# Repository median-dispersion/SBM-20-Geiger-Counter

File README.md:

# SBM-20 Geiger Counter

### ⚠️  DISCLAIMER
This is a hobbyist project and should not be used to accurately determine radiation levels, especially not if those radiation levels are potentially dangerous and or lethal!

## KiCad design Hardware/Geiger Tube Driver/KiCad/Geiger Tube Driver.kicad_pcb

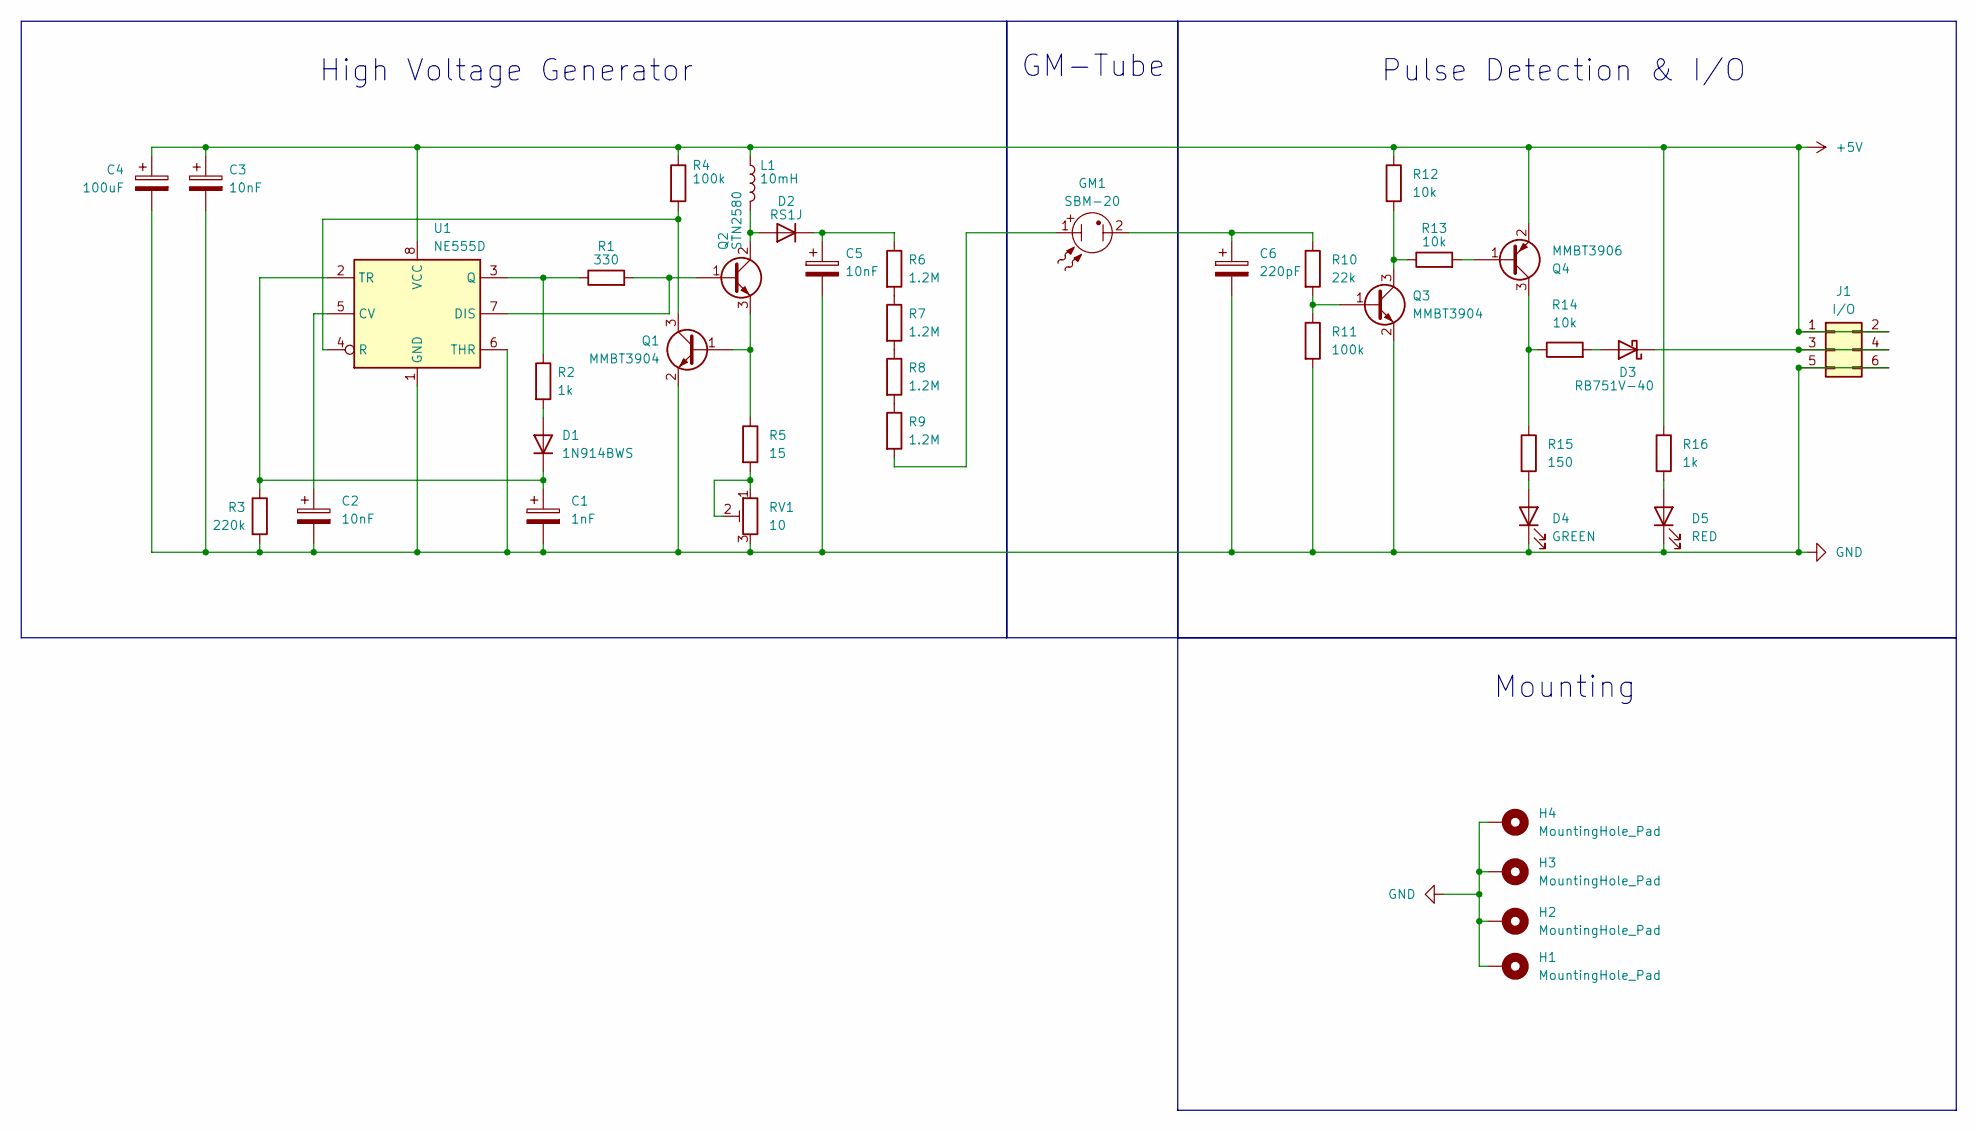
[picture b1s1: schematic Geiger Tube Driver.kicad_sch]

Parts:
C1: 1nF; C_1206_3216Metric_Pad1.33x1.80mm_HandSolder
C2, C3, C5: 10nF; C_1206_3216Metric_Pad1.33x1.80mm_HandSolder
C4: 100uF; CP_Elec_6.3x5.4
C6: 220pF; C_1206_3216Metric_Pad1.33x1.80mm_HandSolder
D1: 1N914BWS; D_SOD-323_HandSoldering
D2: RS1J; SMA_HV_Handsoldering
D3: RB751V-40; D_SOD-323_HandSoldering
D4: GREEN; LED_1206_3216Metric_Pad1.42x1.75mm_HandSolder
D5: RED; LED_1206_3216Metric_Pad1.42x1.75mm_HandSolder
GM1: SBM-20
H1, H2, H3, H4: MountingHole_Pad; MountingHole_3.2mm_M3_Pad_Via
J1: I/O; PinHeader_2x03_P2.54mm_Vertical
L1: 10mH; 8065_Handsoldering
Q1, Q3: MMBT3904; SOT-23_Handsoldering
Q2: STN2580; SOT-223-3_TabPin2
Q4: MMBT3906; SOT-23_Handsoldering
R1: 330; R_1206_3216Metric_Pad1.30x1.75mm_HandSolder
R2, R16: 1k; R_1206_3216Metric_Pad1.30x1.75mm_HandSolder
R3: 220k; R_1206_3216Metric_Pad1.30x1.75mm_HandSolder
R4, R11: 100k; R_1206_3216Metric_Pad1.30x1.75mm_HandSolder
R5: 15; R_1206_3216Metric_Pad1.30x1.75mm_HandSolder
R6, R7, R8, R9: 1.2M; R_1206_3216Metric_Pad1.30x1.75mm_HandSolder
R10: 22k; R_1206_3216Metric_Pad1.30x1.75mm_HandSolder
R12, R13, R14: 10k; R_1206_3216Metric_Pad1.30x1.75mm_HandSolder
R15: 150; R_1206_3216Metric_Pad1.30x1.75mm_HandSolder
RV1: 10; 3361P-1-100GLF
U1: NE555D; SOIC-8_3.9x4.9mm_P1.27mm

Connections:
+5V: C3.1, C4.1, J1.1, J1.2, L1.1, Q4.2 (E), R4.1, R12.1, R16.1, U1.8 (VCC)
GND: C1.2, C2.2, C3.2, C4.2, C5.2, C6.2, D4.1 (K), D5.1 (K), H1.1, H2.1, H3.1, H4.1, J1.5, J1.6, Q1.2 (E), Q3.2 (E), R3.2, R11.2, RV1.3, U1.1 (GND), U1.6 (THR)
unnamed: C6.1, GM1.2, R10.1
unnamed: D1.2 (A), R2.2
unnamed: C1.1, D1.1 (K), R3.1, U1.2 (TR)
unnamed: D2.2 (A), L1.2, Q2.2 (C), Q2.4 (C)
unnamed: C5.1, D2.1 (K), R6.1
unnamed: D3.2 (A), R14.2
unnamed: D3.1 (K), J1.3, J1.4
unnamed: D4.2 (A), R15.2
unnamed: D5.2 (A), R16.2
unnamed: GM1.1, R9.2
unnamed: Q1.1 (B), Q2.3 (E), R5.1
unnamed: Q1.3 (C), R4.2, U1.4 (R)
unnamed: Q2.1 (B), R1.2, U1.7 (DIS)
unnamed: Q3.1 (B), R10.2, R11.1
unnamed: Q3.3 (C), R12.2, R13.1
unnamed: Q4.1 (B), R13.2
unnamed: Q4.3 (C), R14.1, R15.1
unnamed: R5.2, RV1.1, RV1.2
unnamed: R6.2, R7.1
unnamed: R7.2, R8.1
unnamed: R8.2, R9.1
unnamed: C2.1, U1.5 (CV)
unnamed: R1.1, R2.1, U1.3 (Q)

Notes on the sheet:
Pulse Detection & I/O
High Voltage Generator
GM-Tube
Mounting

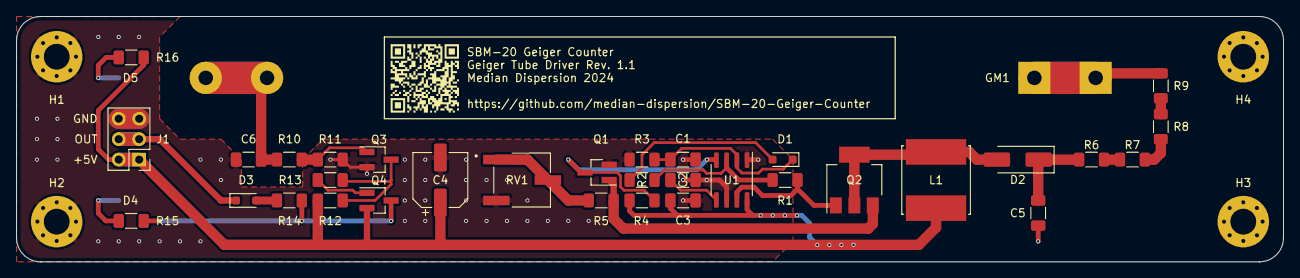
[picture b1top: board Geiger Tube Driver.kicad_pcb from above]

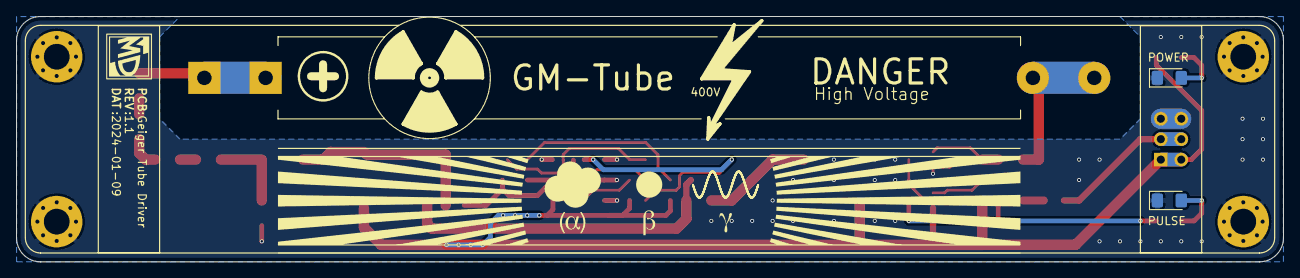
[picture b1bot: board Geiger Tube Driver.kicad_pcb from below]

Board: 2 copper layers, 157.5 x 30.5 mm, 40 parts (3 on the bottom side), 25 nets.

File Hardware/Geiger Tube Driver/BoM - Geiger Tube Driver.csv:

Item,Qty,Reference(s),Value,Footprint,Datasheet,MPN,Digikey (URL),Price (EUR),Price * Qty (EUR)
1,1,C1,1nF,Capacitor_SMD:C_1206_3216Metric_Pad1.33x1.80mm_HandSolder,https://www.we-online.com/katalog/datasheet/885012208046.pdf,885012208046,https://www.digikey.de/de/products/detail/w%C3%BCrth-elektro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,"0,09€","0,09€"
2,2,"C2, C3",10nF,Capacitor_SMD:C_1206_3216Metric_Pad1.33x1.80mm_HandSolder,https://www.we-online.com/katalog/datasheet/885012208112.pdf,885012208112,https://www.digikey.de/de/products/detail/w%C3%BCrth-elektro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,"0,10€","0,20€"
3,1,C4,100uF,Capacitor_SMD:CP_Elec_6.3x5.4,https://www.we-online.com/katalog/datasheet/865080243007.pdf,865080243007,https://www.digikey.de/de/products/detail/w%C3%BCrth-elektro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,"0,27€","0,27€"
4,1,C5,10nF,Capacitor_SMD:C_1206_3216Metric_Pad1.33x1.80mm_HandSolder,https://www.we-online.com/katalog/datasheet/885342208021.pdf,885342208021,https://www.digikey.de/de/products/detail/w%C3%BCrth-elektro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,"0,23€","0,23€"
5,1,C6,220pF,Capacitor_SMD:C_1206_3216Metric_Pad1.33x1.80mm_HandSolder,https://www.samsungsem.com/kr/support/product-search/mlcc/CL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,CL31C221JIHNFNE,https://www.digikey.de/de/products/detail/samsung-electro-me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,"0,26€","0,26€"
6,1,D1,1N914BWS,Diode_SMD:D_SOD-323_HandSoldering,https://rocelec.widen.net/view/pdf/tf3dlteblx/FAIR-S-A000057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,1N914BWS,https://www.digikey.de/de/products/detail/onsemi/1N914BWS/1873807,"0,17€","0,17€"
7,1,D2,RS1J,Footprints:SMA_HV_Handsoldering,https://www.diodes.com/assets/Datasheets/ds15002.pdf,RS1J-13-F,https://www.digikey.de/de/products/detail/diodes-incorporate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,"0,42€","0,42€"
8,1,D3,RB751V-40,Diode_SMD:D_SOD-323_HandSoldering,https://www.panjit.com.tw/upload/datasheet/RB751V-40.pdf,RB751V-40_R1_00001,https://www.digikey.de/de/products/detail/panjit-internation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,"0,17€","0,17€"
9,1,D4,GREEN,LED_SMD:LED_1206_3216Metric_Pad1.42x1.75mm_HandSolder,https://www.we-online.com/katalog/datasheet/150120GS75000.pdf,150120GS75000,https://www.digikey.de/de/products/detail/w%C3%BCrth-elektro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,"0,21€","0,21€"
10,1,D5,RED,LED_SMD:LED_1206_3216Metric_Pad1.42x1.75mm_HandSolder,https://www.we-online.com/katalog/datasheet/150120RS75000.pdf,150120RS75000,https://www.digikey.de/de/products/detail/w%C3%BCrth-elektro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,"0,21€","0,21€"
11,1,GM1,SBM-20,Footprints:SBM-20,https://www.belfuse.com/resources/datasheets/circuitprotecti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,FC-102 BRIGHT TIN,https://www.digikey.de/de/products/detail/bel-fuse-inc/FC-10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,"0,17€","0,17€"
12,1,J1,I/O,Connector_PinHeader_2.54mm:PinHeader_2x03_P2.54mm_Vertical,https://app.adam-tech.com/products/download/data_sheet/20206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,PH2-06-UA,https://www.digikey.de/de/products/detail/adam-tech/PH2-06-U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,"0,12€","0,12€"
13,1,L1,10mH,Footprints:8065_Handsoldering,https://www.we-online.com/katalog/datasheet/74404086103.pdf,74404086103,https://www.digikey.de/de/products/detail/w%C3%BCrth-elektro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,"1,17€","1,17€"
14,2,"Q1, Q3",MMBT3904,Package_TO_SOT_SMD:SOT-23_Handsoldering,https://goodarksemi.com/docs/datasheets/transistors/MMBT3904.pdf,MMBT3904,https://www.digikey.de/de/products/detail/good-ark-semicondu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,"0,09€","0,18€"
15,1,Q2,STN2580,Package_TO_SOT_SMD:SOT-223,https://www.st.com/content/ccc/resource/technical/document/d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,STN2580,https://www.digikey.de/de/products/detail/stmicroelectronics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,"0,62€","0,62€"
16,1,Q4,MMBT3906,Package_TO_SOT_SMD:SOT-23_Handsoldering,https://goodarksemi.com/docs/datasheets/transistors/MMBT3906.pdf,MMBT3906,https://www.digikey.de/de/products/detail/good-ark-semicondu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,"0,09€","0,09€"
17,1,R1,330,Resistor_SMD:R_1206_3216Metric_Pad1.30x1.75mm_HandSolder,https://www.yageo.com/upload/media/product/productsearch/dat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,RC1206FR-07330RL,https://www.digikey.de/de/products/detail/yageo/RC1206FR-073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,"0,09€","0,09€"
18,2,"R2, R16",1k,Resistor_SMD:R_1206_3216Metric_Pad1.30x1.75mm_HandSolder,https://www.yageo.com/upload/media/product/productsearch/dat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,RC1206FR-071KL,https://www.digikey.de/de/products/detail/yageo/RC1206FR-071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,"0,09€","0,18€"
19,1,R3,220k,Resistor_SMD:R_1206_3216Metric_Pad1.30x1.75mm_HandSolder,https://www.yageo.com/upload/media/product/productsearch/dat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,RC1206FR-07220KL,https://www.digikey.de/de/products/detail/yageo/RC1206FR-072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,"0,09€","0,09€"
20,2,"R4, R11",100k,Resistor_SMD:R_1206_3216Metric_Pad1.30x1.75mm_HandSolder,https://www.yageo.com/upload/media/product/productsearch/dat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,AC1206FR-07100KL,https://www.digikey.de/de/products/detail/yageo/AC1206FR-071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,"0,09€","0,18€"
21,1,R5,15,Resistor_SMD:R_1206_3216Metric_Pad1.30x1.75mm_HandSolder,https://www.yageo.com/upload/media/product/productsearch/dat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,RC1206FR-0715RL,https://www.digikey.de/de/products/detail/yageo/RC1206FR-071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,"0,09€","0,09€"
22,4,"R6, R7, R8, R9",1.2M,Resistor_SMD:R_1206_3216Metric_Pad1.30x1.75mm_HandSolder,https://www.yageo.com/upload/media/product/productsearch/dat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,RC1206FR-071M2L,https://www.digikey.de/de/products/detail/yageo/RC1206FR-071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,"0,09€","0,36€"
23,1,R10,22k,Resistor_SMD:R_1206_3216Metric_Pad1.30x1.75mm_HandSolder,https://www.yageo.com/upload/media/product/productsearch/dat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,RC1206FR-0722KL,https://www.digikey.de/de/products/detail/yageo/RC1206FR-072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,"0,09€","0,09€"
24,3,"R12, R13, R14",10k,Resistor_SMD:R_1206_3216Metric_Pad1.30x1.75mm_HandSolder,https://www.yageo.com/upload/media/product/productsearch/dat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,RC1206FR-1310KL,https://www.digikey.de/de/products/detail/yageo/RC1206FR-131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,"0,09€","0,27€"
25,1,R15,150,Resistor_SMD:R_1206_3216Metric_Pad1.30x1.75mm_HandSolder,https://www.yageo.com/upload/media/product/productsearch/dat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,RC1206FR-13150RL,https://www.digikey.de/de/products/detail/yageo/RC1206FR-131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,"0,09€","0,09€"
26,1,RV1,10,Footprints:3361P-1-100GLF,https://www.bourns.com/docs/Product-Datasheets/3361.pdf,3361P-1-100GLF,https://www.digikey.de/de/products/detail/bourns-inc/3361P-1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,"1,17€","1,17€"
27,1,U1,NE555D,Package_SO:SOIC-8_3.9x4.9mm_P1.27mm,https://rocelec.widen.net/view/pdf/giqzbewdkx/slfs022i.pdf?t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,NE555D,https://www.digikey.de/de/products/detail/texas-instruments/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,"0,59€","0,59€"
28,4,"H1, H2, H3, H4",M3 Bolt,Footprints:MountingHole_3.2mm_M3_Pad_Via,~,~,~,"0,00€","0,00€"

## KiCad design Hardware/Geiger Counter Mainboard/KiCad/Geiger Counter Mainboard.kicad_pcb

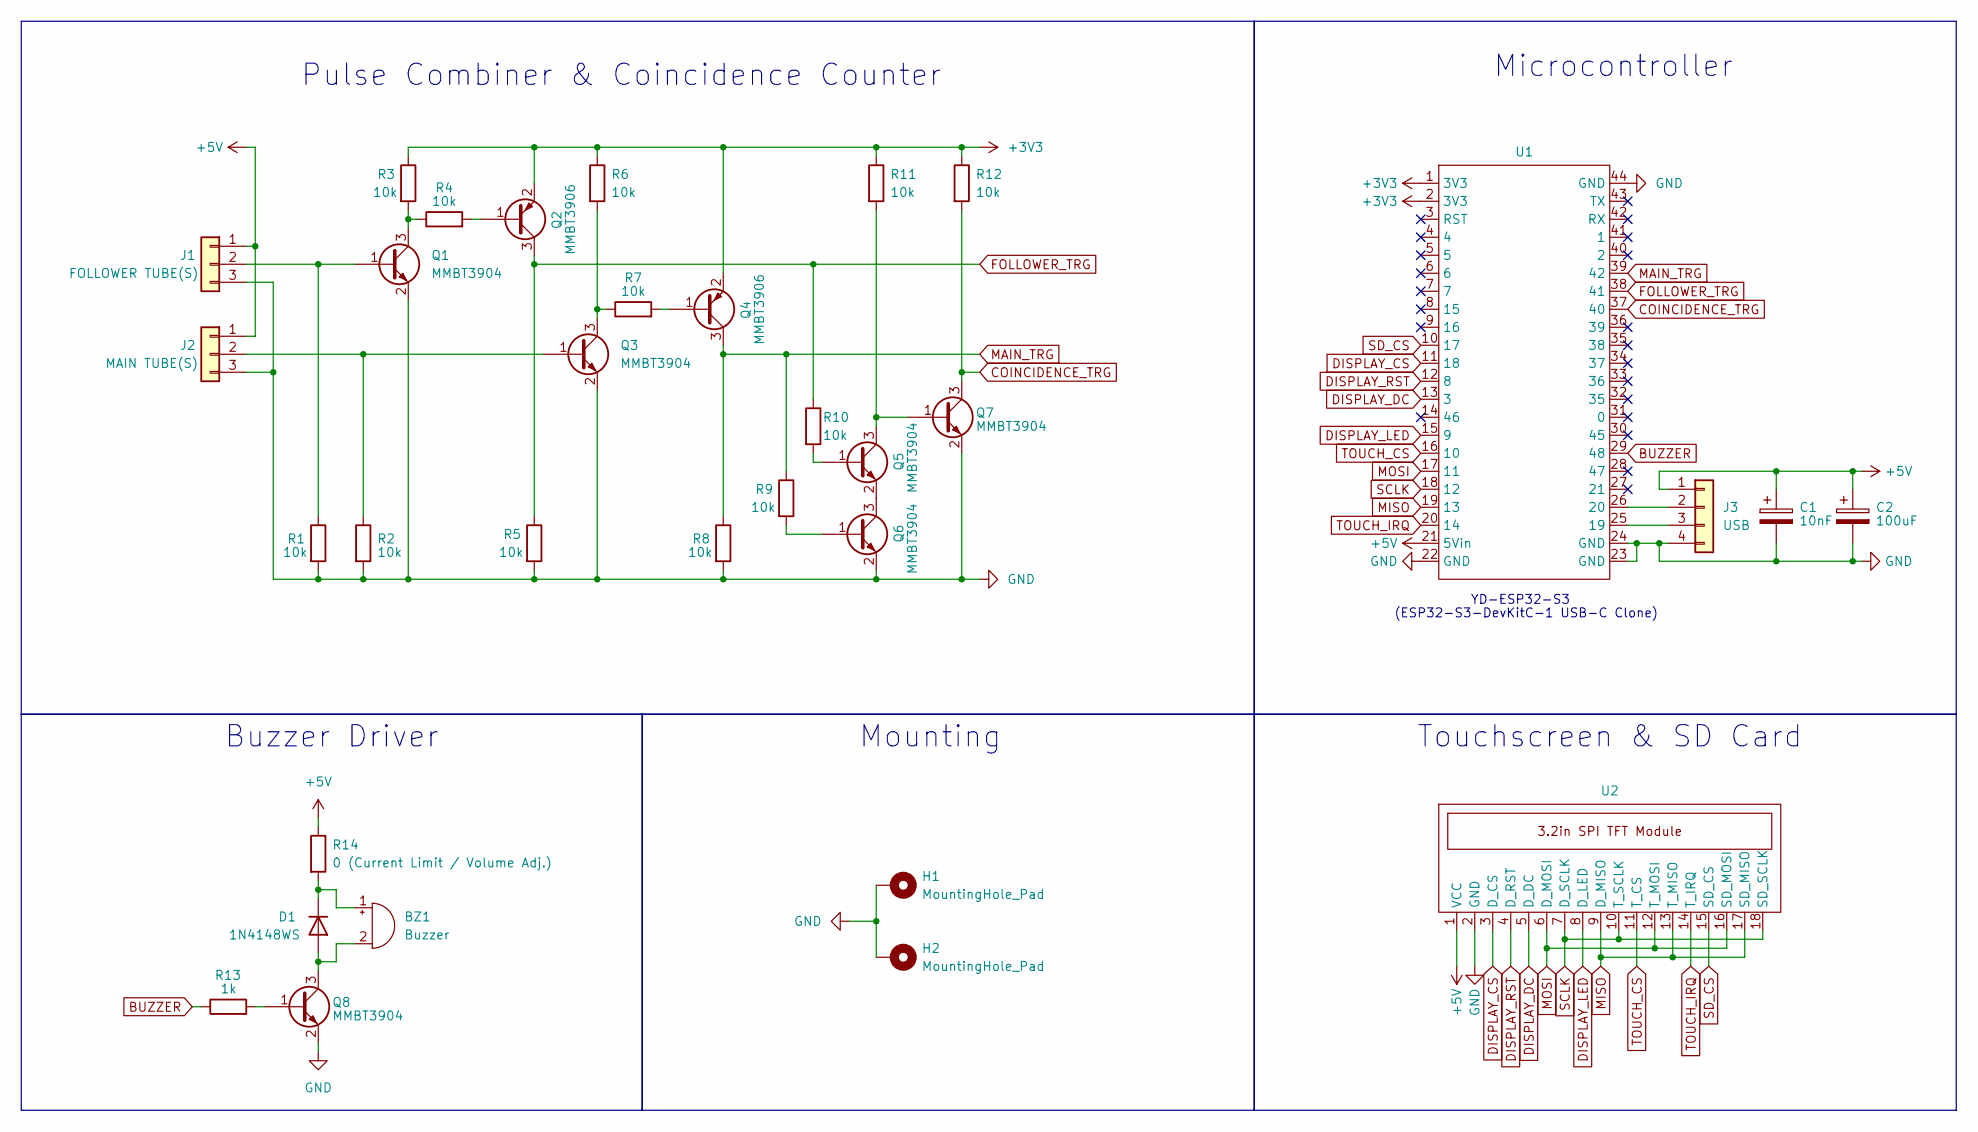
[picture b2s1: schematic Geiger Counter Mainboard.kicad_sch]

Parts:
BZ1: Buzzer; PinHeader_1x02_P2.54mm_Vertical
C1: 10nF; C_1206_3216Metric_Pad1.33x1.80mm_HandSolder
C2: 100uF; CP_Elec_6.3x5.4
D1: 1N4148WS; D_SOD-323_HandSoldering
H1, H2: MountingHole_Pad; MountingHole_3.2mm_M3_Pad_Via
J1: FOLLOWER TUBE(S); PinHeader_1x03_P2.54mm_Vertical
J2: MAIN TUBE(S); PinHeader_1x03_P2.54mm_Vertical
J3: USB; PinHeader_1x04_P2.54mm_Vertical
Q1, Q3, Q5, Q6, Q7, Q8: MMBT3904; SOT-23_Handsoldering
Q2, Q4: MMBT3906; SOT-23_Handsoldering
R1, R2, R3, R4, R5, R6, R7, R8, R9, R10, R11, R12: 10k; R_1206_3216Metric_Pad1.30x1.75mm_HandSolder
R13: 1k; R_1206_3216Metric_Pad1.30x1.75mm_HandSolder
R14: 0 (Current Limit / Volume Adj.); R_1206_3216Metric_Pad1.30x1.75mm_HandSolder
U1: YD-ESP32-S3 (ESP32-S3-DevKitC-1 USB-C Clone)
U2: 3.2in SPI TFT Touch Module

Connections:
+3V3: Q2.2 (E), Q4.2 (E), R3.1, R6.1, R11.1, R12.1, U1.1 (3V3), U1.2 (3V3)
+5V: C1.1, C2.1, J1.1, J2.1, J3.1, R14.1, U1.21 (5Vin), U2.1 (VCC)
BUZZER: R13.1, U1.29 (48)
COINCIDENCE_TRG: Q7.3 (C), R12.2, U1.37 (40)
DISPLAY_CS: U1.11 (18), U2.3 (D_CS)
DISPLAY_DC: U1.13 (3), U2.5 (D_DC)
DISPLAY_LED: U1.15 (9), U2.8 (D_LED)
DISPLAY_RST: U1.12 (8), U2.4 (D_RST)
FOLLOWER_TRG: Q2.3 (C), R5.1, R10.1, U1.38 (41)
GND: C1.2, C2.2, H1.1, H2.1, J1.3, J2.3, J3.4, Q1.2 (E), Q3.2 (E), Q6.2 (E), Q7.2 (E), Q8.2 (E), R1.2, R2.2, R5.2, R8.2, U1.22 (GND), U1.23 (GND), U1.24 (GND), U1.44 (GND), U2.2 (GND)
MAIN_TRG: Q4.3 (C), R8.1, R9.1, U1.39 (42)
MISO: U1.19 (13), U2.9 (D_MISO), U2.13 (T_MISO), U2.17 (SD_MISO)
MOSI: U1.17 (11), U2.6 (D_MOSI), U2.12 (T_MOSI), U2.16 (SD_MOSI)
unnamed: BZ1.2 (+), D1.2 (A), Q8.3 (C)
unnamed: BZ1.1 (-), D1.1 (K), R14.2
unnamed: J1.2, Q1.1 (B), R1.1
unnamed: J2.2, Q3.1 (B), R2.1
unnamed: J3.2, U1.26 (20)
unnamed: J3.3, U1.25 (19)
unnamed: Q1.3 (C), R3.2, R4.1
unnamed: Q2.1 (B), R4.2
unnamed: Q3.3 (C), R6.2, R7.1
unnamed: Q4.1 (B), R7.2
unnamed: Q5.1 (B), R10.2
unnamed: Q5.3 (C), Q7.1 (B), R11.2
unnamed: Q5.2 (E), Q6.3 (C)
unnamed: Q6.1 (B), R9.2
unnamed: Q8.1 (B), R13.2
SCLK: U1.18 (12), U2.7 (D_SCLK), U2.10 (T_SCLK), U2.18 (SD_SCLK)
SD_CS: U1.10 (17), U2.15 (SD_CS)
TOUCH_CS: U1.16 (10), U2.11 (T_CS)
TOUCH_IRQ: U1.20 (14), U2.14 (T_IRQ)

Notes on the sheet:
Pulse Combiner & Coincidence Counter
(ESP32-S3-DevKitC-1 USB-C Clone)
Buzzer Driver
Microcontroller
Mounting
Touchscreen & SD Card
YD-ESP32-S3

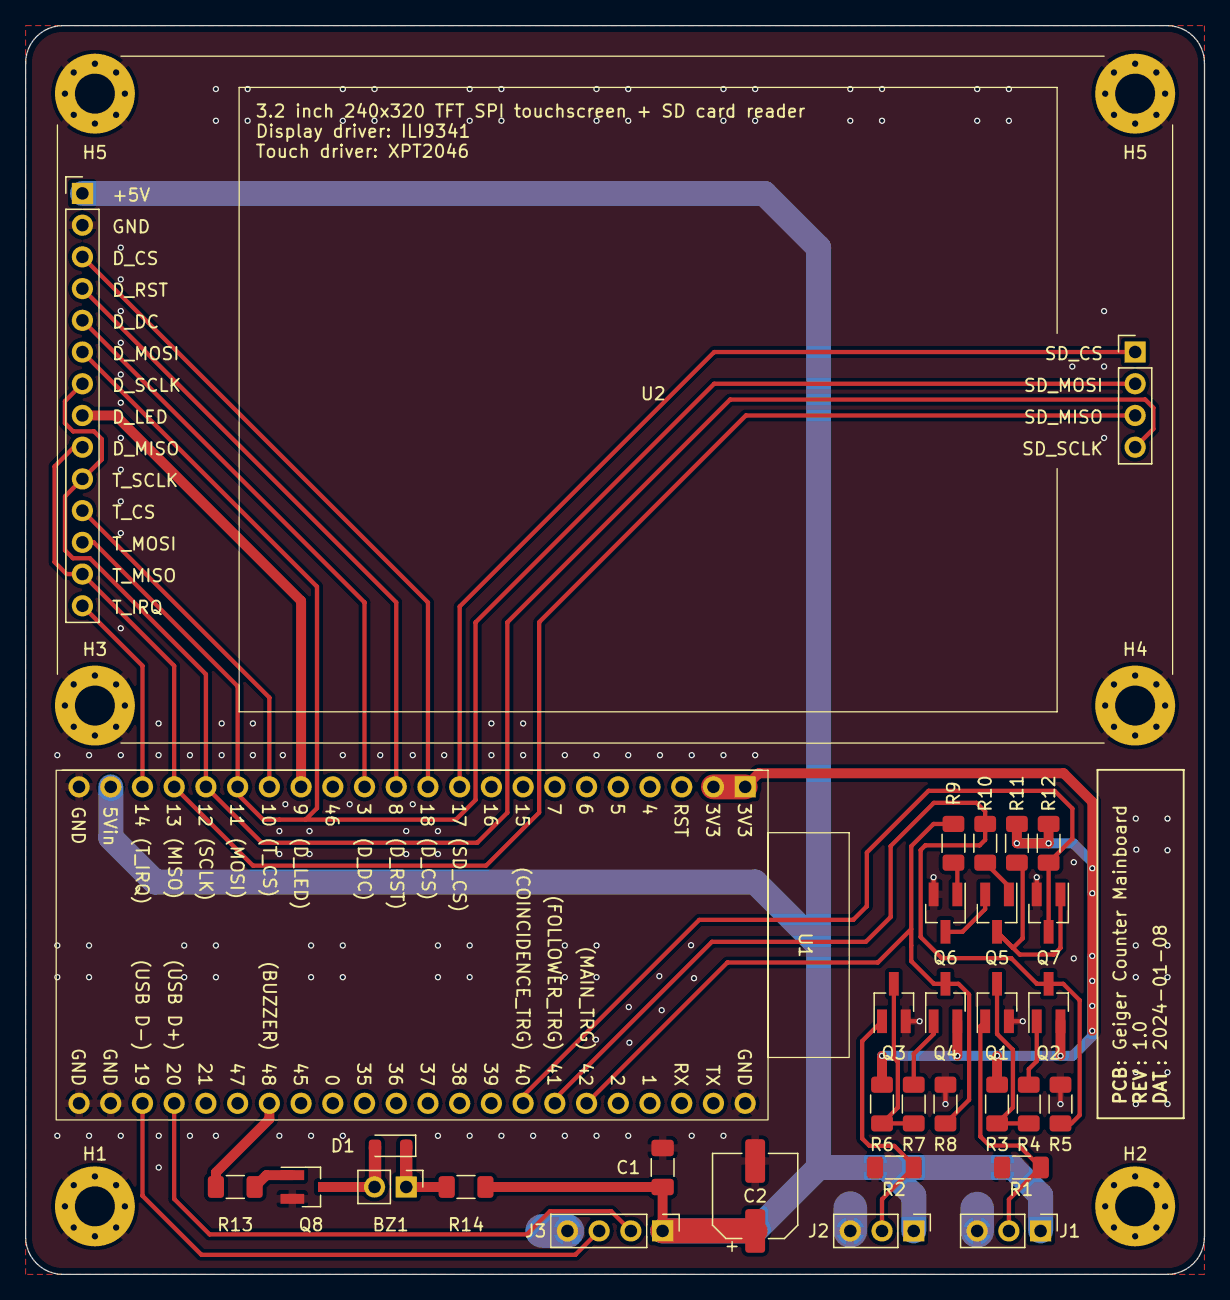
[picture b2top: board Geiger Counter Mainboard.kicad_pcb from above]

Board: 2 copper layers, 94.4 x 100.0 mm, 33 parts (0 on the bottom side), 32 nets.

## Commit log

2023-09-21 Added files for the Geiger tube driver board.
2023-12-29 Removed unnecessary files
2023-12-29 Added .gitignore
2023-12-29 Geiger Tube Driver Rev 1.1
2023-12-30 Adjusted mounting hole spacing
2023-12-30 Added mainboard schematic
2023-12-31 Fixed BoM
2024-01-02 Updated TFT module footprint
2024-01-02 Updated TFT module footprint & schematic
2024-01-07 Updated schematic & set PCB properties
2024-01-07 Added PCB for mainboard
2024-01-07 Organized schematics & rounded PCB corners
2024-01-08 Finalizing Mainboard
2024-01-09 Updated silkscreen
